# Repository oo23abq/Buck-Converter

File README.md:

# Basic-Buck-Converter-PCB

This repository contains the full design, simulation, documentation, and PCB layout for a compact buck (step‑down) DC‑DC converter. It is intended as a small, practical companion board to a more advanced isolated flyback converter, providing a simple, efficient, and well‑documented reference design for low‑voltage power conversion.

The project includes LTspice simulations, KiCad schematic + PCB, design calculations, and live testing and wiring. 
🔧 Project Overview

The board will take a DC input and step it down to low‑voltage output using a synchronous switching topology. 

Design Focuses: 

* Compact PCB footprint
* Good efficiency across a wide input range
* Clean documentation and reproducible calculations
* Practical testability (scope points, connectors, PG indicator)

Recruiter‑friendly presentation on GitHub

🎯 Target Electrical Specifications
* Parameter	Target
* Input Voltage	7–24 V DC
* Output Voltage	5 V (adjustable via feedback divider)
* Output Current	1–2 A depending on regulator choice
* Switching Frequency	500 kHz – 2 MHz (IC‑dependent)
* Duty Cycle ≈ 0.42
* Output Ripple	≤ 50 mVpp
* Inductor Ripple	20–40% of Iout

These values will be refined once the LTspice schematic is finalised.

📐 LTspice Simulations Included

The following was simulated fully in LTspice: 

* Output voltage regulation
* Output ripple measurement
* Inductor current ripple
* Switch node waveform
* Startup behaviour
* Load step response
* Line step response
* Efficiency vs load sweep

## Repository Structure

```text
├── docs/                               # General Documentation 
│   └── testreport.docx                 # Lab Test Report
├── kicad/                              # KiCAD Project Files 
│   ├── Buck Converter.kicad_pcb        # PCB Board File 
│   ├── Buck Converter.kicad_sch        # Schematic File 
│   ├── bom.csv                         # Bill of Materials
│   ├── gerber/                         # Manufacturing Files 
│   │   └── buck.zip                    # Gerber, NC Drill Files 
│   └── images/                         # 3D PCB Renders 
│       ├── buckconverterbottom.png     # Bottom Layer
│       └── buckconvertertop.png        # Top Layer 
├── ltspice/                            # Analog Simulation Files 
│   ├── models.asc                      # Component Models 
│   └── schematic.asc                   # LTspice schematic
├── testing/                            # Lab Testing
│   ├── oscilloscopeinput.png           # Input Ripple Waveforms 
│   ├── oscilloscopeoutput.png          # Output transient response waveform
│   └── testsetup.png                   # Bench Test Setup 
├── LICENSE                             # MIT Licence File 
└── README.md                           # Guidance / info

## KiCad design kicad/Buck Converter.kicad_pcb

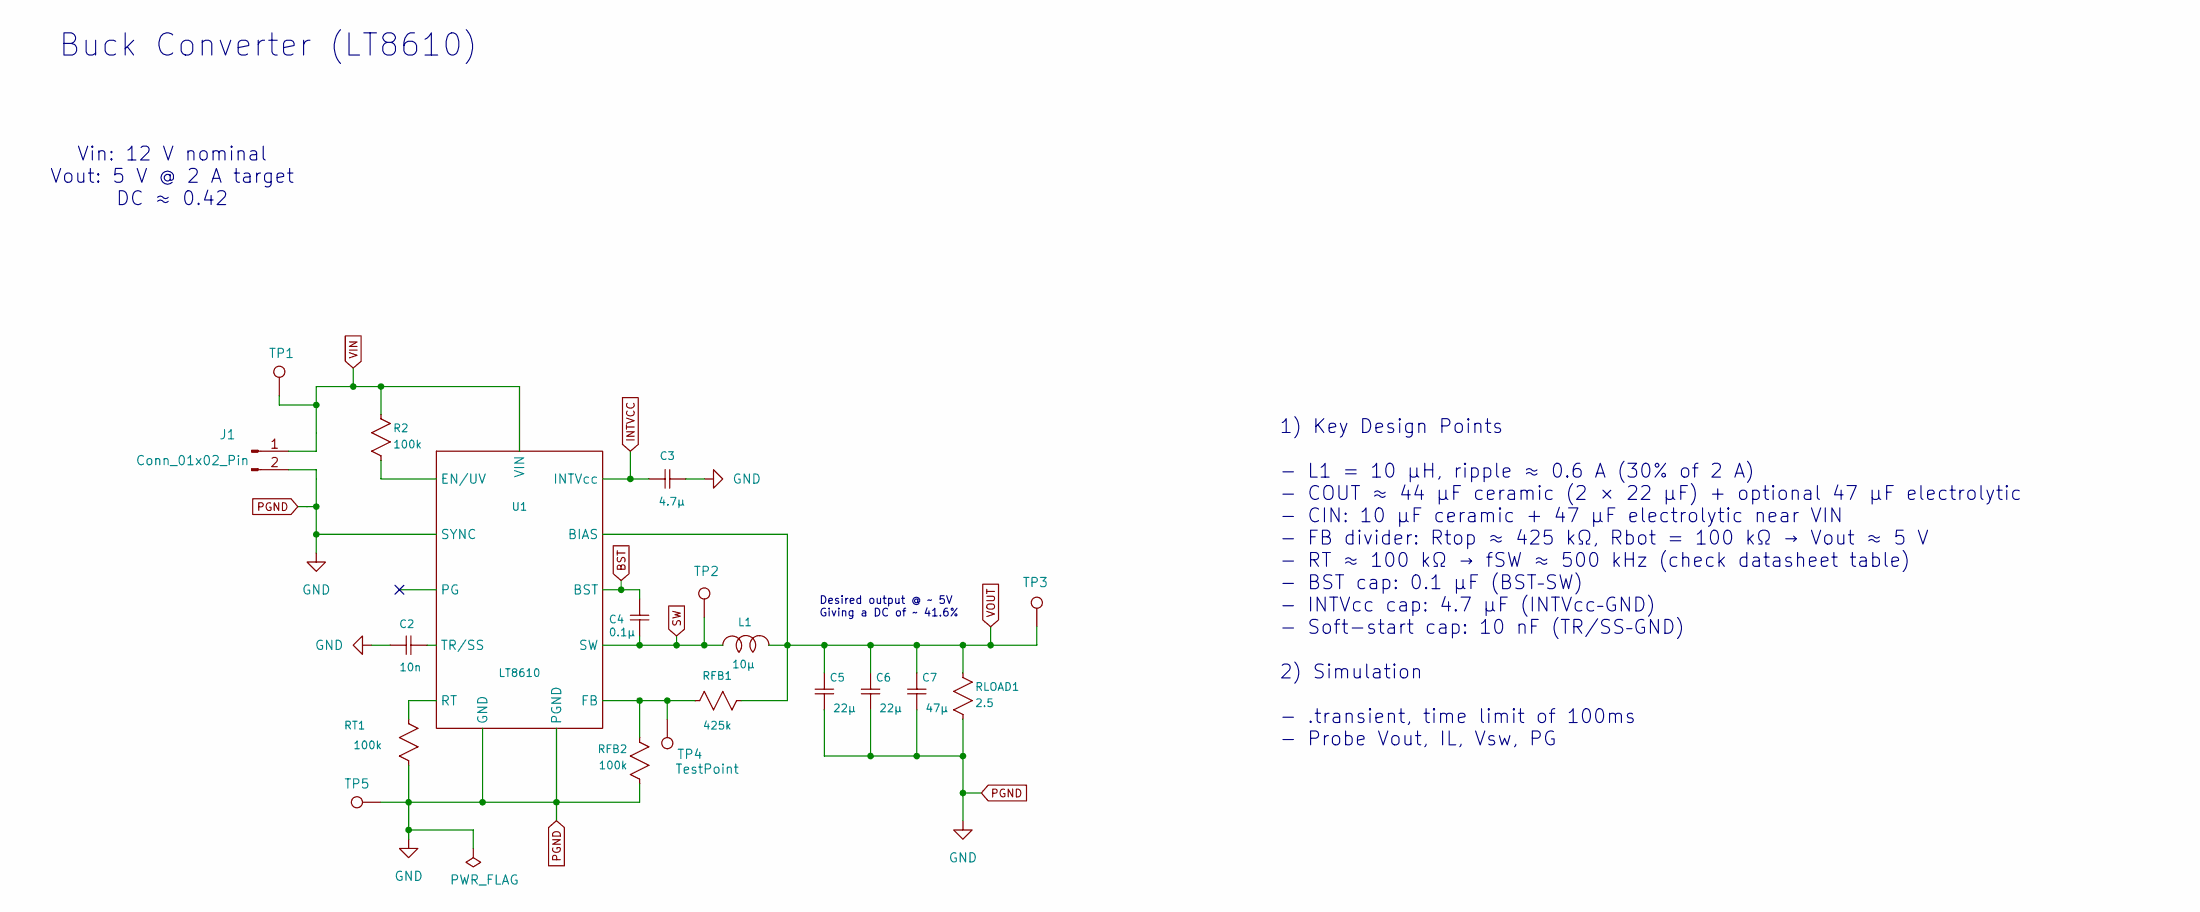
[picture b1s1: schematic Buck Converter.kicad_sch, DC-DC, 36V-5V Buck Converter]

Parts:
C2: 10n; C_0201_0603Metric
C3: 4.7µ; C_0805_2012Metric
C4: 0.1µ; C_0201_0603Metric
C5, C6: 22µ; C_1210_3225Metric
C7: 47µ; C_1210_3225Metric
J1: Conn_01x02_Pin; TerminalBlock_Phoenix_MKDS-1,5-2-5.08_1x02_P5.08mm_Horizont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
L1: 10µ; L_Neosid_SMS-ME3015
R2: 100k; R_0201_0603Metric
RFB1: 425k; R_0201_0603Metric
RFB2: 100k; R_0201_0603Metric
RLOAD1: 2.5; R_1206_3216Metric
RT1: 100k; R_0201_0603Metric
TP1, TP2, TP3, TP4, TP5: TestPoint; TestPoint_Pad_1.0x1.0mm
U1: LT8610; QFN-16-1EP_1.8x2.6mm_P0.4mm_EP0.7x1.5mm

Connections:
BST: C4.1, U1.8 (BST)
INTVCC: C3.1, U1.9 (INTVcc)
unnamed: R2.2, U1.4 (EN/UV)
unnamed: RFB1.1, RFB2.2, TP4.1, U1.12 (FB)
unnamed: RT1.1, U1.3 (RT)
unnamed: C2.1, U1.2 (TR/SS)
PGND: C2.2, C3.2, C5.2, C6.2, C7.2, J1.2, RFB2.1, RLOAD1.2, RT1.2, TP5.1, U1.1 (SYNC), U1.6 (PGND), U1.13 (GND)
SW: C4.2, L1.1, TP2.1, U1.7 (SW)
VIN: J1.1, R2.1, TP1.1, U1.5 (VIN)
VOUT: C5.1, C6.1, C7.1, L1.2, RFB1.2, RLOAD1.1, TP3.1, U1.10 (BIAS)

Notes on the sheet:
Desired output @ ~ 5V Giving a DC of ~ 41.6%
Buck Converter (LT8610)
Vin: 12 V nominal Vout: 5 V @ 2 A target DC ≈ 0.42
1) Key Design Points - L1 = 10 µH, ripple ≈ 0.6 A (30% of 2 A) - COUT ≈ 44 µF ceramic (2 × 22 µF) + optional 47 µF electrolytic - CIN: 10 µF ceramic + 47 µF electrolytic near VIN - FB divider: Rtop ≈ 425 kΩ, Rbot = 100 kΩ → Vout ≈ 5 V - RT ≈ 100 kΩ → fSW ≈ 500 kHz (check datasheet table) - BST cap: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

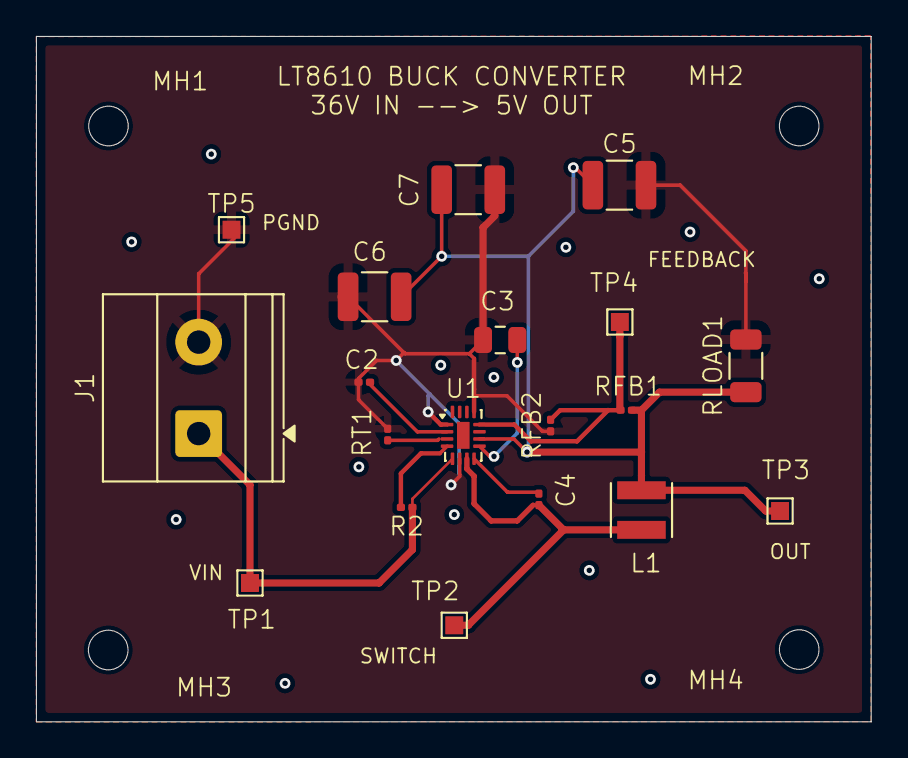
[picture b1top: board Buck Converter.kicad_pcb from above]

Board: 2 copper layers, 46.4 x 38.1 mm, 23 parts (0 on the bottom side), 10 nets.

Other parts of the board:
MH1, MH2, MH3, MH4: MountingHole_2.2mm_M2

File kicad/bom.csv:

"Reference","Qty","Value","DNP","Exclude from BOM","Exclude from Board","Footprint","Datasheet"
"C2","1","10n","","","","Capacitor_SMD:C_0201_0603Metric",""
"C3","1","4.7µ","","","","Capacitor_SMD:C_0805_2012Metric",""
"C4","1","0.1µ","","","","Capacitor_SMD:C_0201_0603Metric",""
"C5,C6","2","22µ","","","","Capacitor_SMD:C_1210_3225Metric",""
"C7","1","47µ","","","","Capacitor_SMD:C_1210_3225Metric",""
"J1","1","Conn_01x02_Pin","","","","TerminalBlock_Phoenix:TerminalBlock_Phoenix_MKDS-1,5-2-5.08_1x02_P5.08mm_Horizontal","~"
"L1","1","10µ","","","","Inductor_SMD:L_Neosid_SMS-ME3015",""
"R2,RFB2,RT1","3","100k","","","","Resistor_SMD:R_0201_0603Metric",""
"RFB1","1","425k","","","","Resistor_SMD:R_0201_0603Metric",""
"RLOAD1","1","2.5","","","","Resistor_SMD:R_1206_3216Metric",""
"TP1,TP2,TP3,TP4,TP5","5","TestPoint","","","","TestPoint:TestPoint_Pad_1.0x1.0mm","~"
"U1","1","LT8610","","","","Package_DFN_QFN:QFN-16-1EP_1.8x2.6mm_P0.4mm_EP0.7x1.5mm",""
